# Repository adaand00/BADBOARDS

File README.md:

# BADBOARDS
 Useless keyboards
 
## Current boards

### BB-1 ASCIISTICK
Back to the roots. Gain full control with raw ascii input.

### BB-2 GRIDNAVIGATOR
*Etch-a-sketch* for the 21st century. This keyboard even has additional mouse input.

## Future keyboards

- [ ] One key morse code
- [ ] ascending letters + next
- [ ] Slot machine letters
- [ ] Joystick
- [ ] Frequency control
- [ ] Flute
- [ ] Accelerometer
- [ ] Advanced control panel
- [ ] Shrek

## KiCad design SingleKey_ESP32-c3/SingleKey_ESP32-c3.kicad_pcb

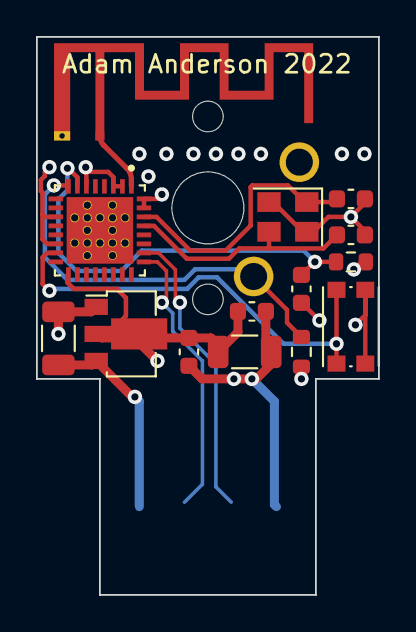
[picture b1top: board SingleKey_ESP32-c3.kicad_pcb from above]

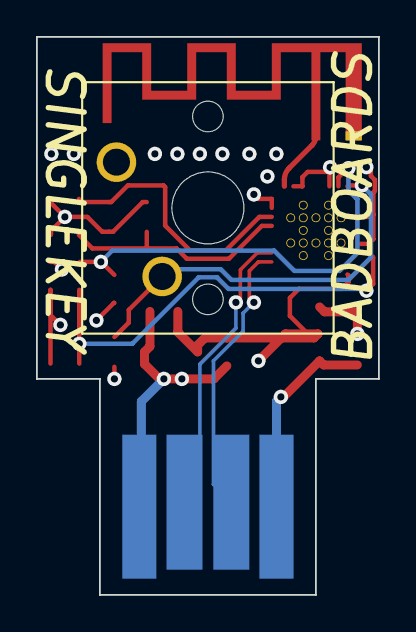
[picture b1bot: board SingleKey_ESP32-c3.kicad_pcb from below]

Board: 4 copper layers, 19.0 x 31.0 mm, 16 parts (2 on the bottom side), 11 nets.

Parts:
AE1: Antenna; Texas_SWRA117D_2.4GHz_Right
C1, C2: 10pF; C_0603_1608Metric
C3, C4: 100n; C_0603_1608Metric
C5: 1uF; C_0603_1608Metric
C7, C8: 10uF; C_1206_3216Metric
J1: USB_A; CONN-USB-A-PCB-TRACES
R1, R2: 1k; R_0603_1608Metric
SW1: SW_Push; SW_Cherry_MX_1.00u_PCB
SW3: SW_Push; SW_Push_1P1T_NO_CK_KMR2
U1: ESP32-C3FH4; QFN50P500X500X90-33N
U2: LM1117-3.3; SOT-89-3
Y1: Crystal_GND24; Oscillator_SMD_Abracon_ASE-4Pin_3.2x2.5mm

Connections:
+3V3: C4.1, C5.1, C8.1, R1.1, R2.1, U1.2 (VDD3P3), U1.3 (VDD3P3), U1.6 (GPIO2), U1.11 (VDD3P3_RTC), U1.14 (GPIO8), U1.17 (VDD3P3_CPU), U1.31 (VDDA), U1.32 (VDDA), U2.2 (VO)
+5V: C7.1, J1.1 (VBUS), U2.3 (VI)
/ANT: AE1.1 (FEED), U1.1 (LNA_IN)
/BTN: R2.2, SW1.2, U1.8 (GPIO3)
/USB_D+: J1.3 (D+), U1.26 (GPIO19)
/USB_D-: J1.2 (D-), U1.25 (GPIO18)
Earth: AE1.2 (PCB_Trace), C1.1, C2.2, C3.2, C4.2, C5.2, C7.2, C8.2, J1.4 (GND), SW1.1, SW3.2, U1.33 (GND), U1.34, U1.35, U1.36, U1.37, U1.38, U1.39, U1.40, U1.41, U1.42, U1.43, U1.44, U1.45, U1.46, U1.47, U1.48, U1.49, U2.1 (GND), Y1.2, Y1.4
unnamed: C1.2, U1.30 (XTAL_P), Y1.1
unnamed: C2.1, U1.29 (XTAL_N), Y1.3
unnamed: C3.1, R1.2, U1.7 (CHIP_EN)
unnamed: SW3.1, U1.15 (GPIO9)

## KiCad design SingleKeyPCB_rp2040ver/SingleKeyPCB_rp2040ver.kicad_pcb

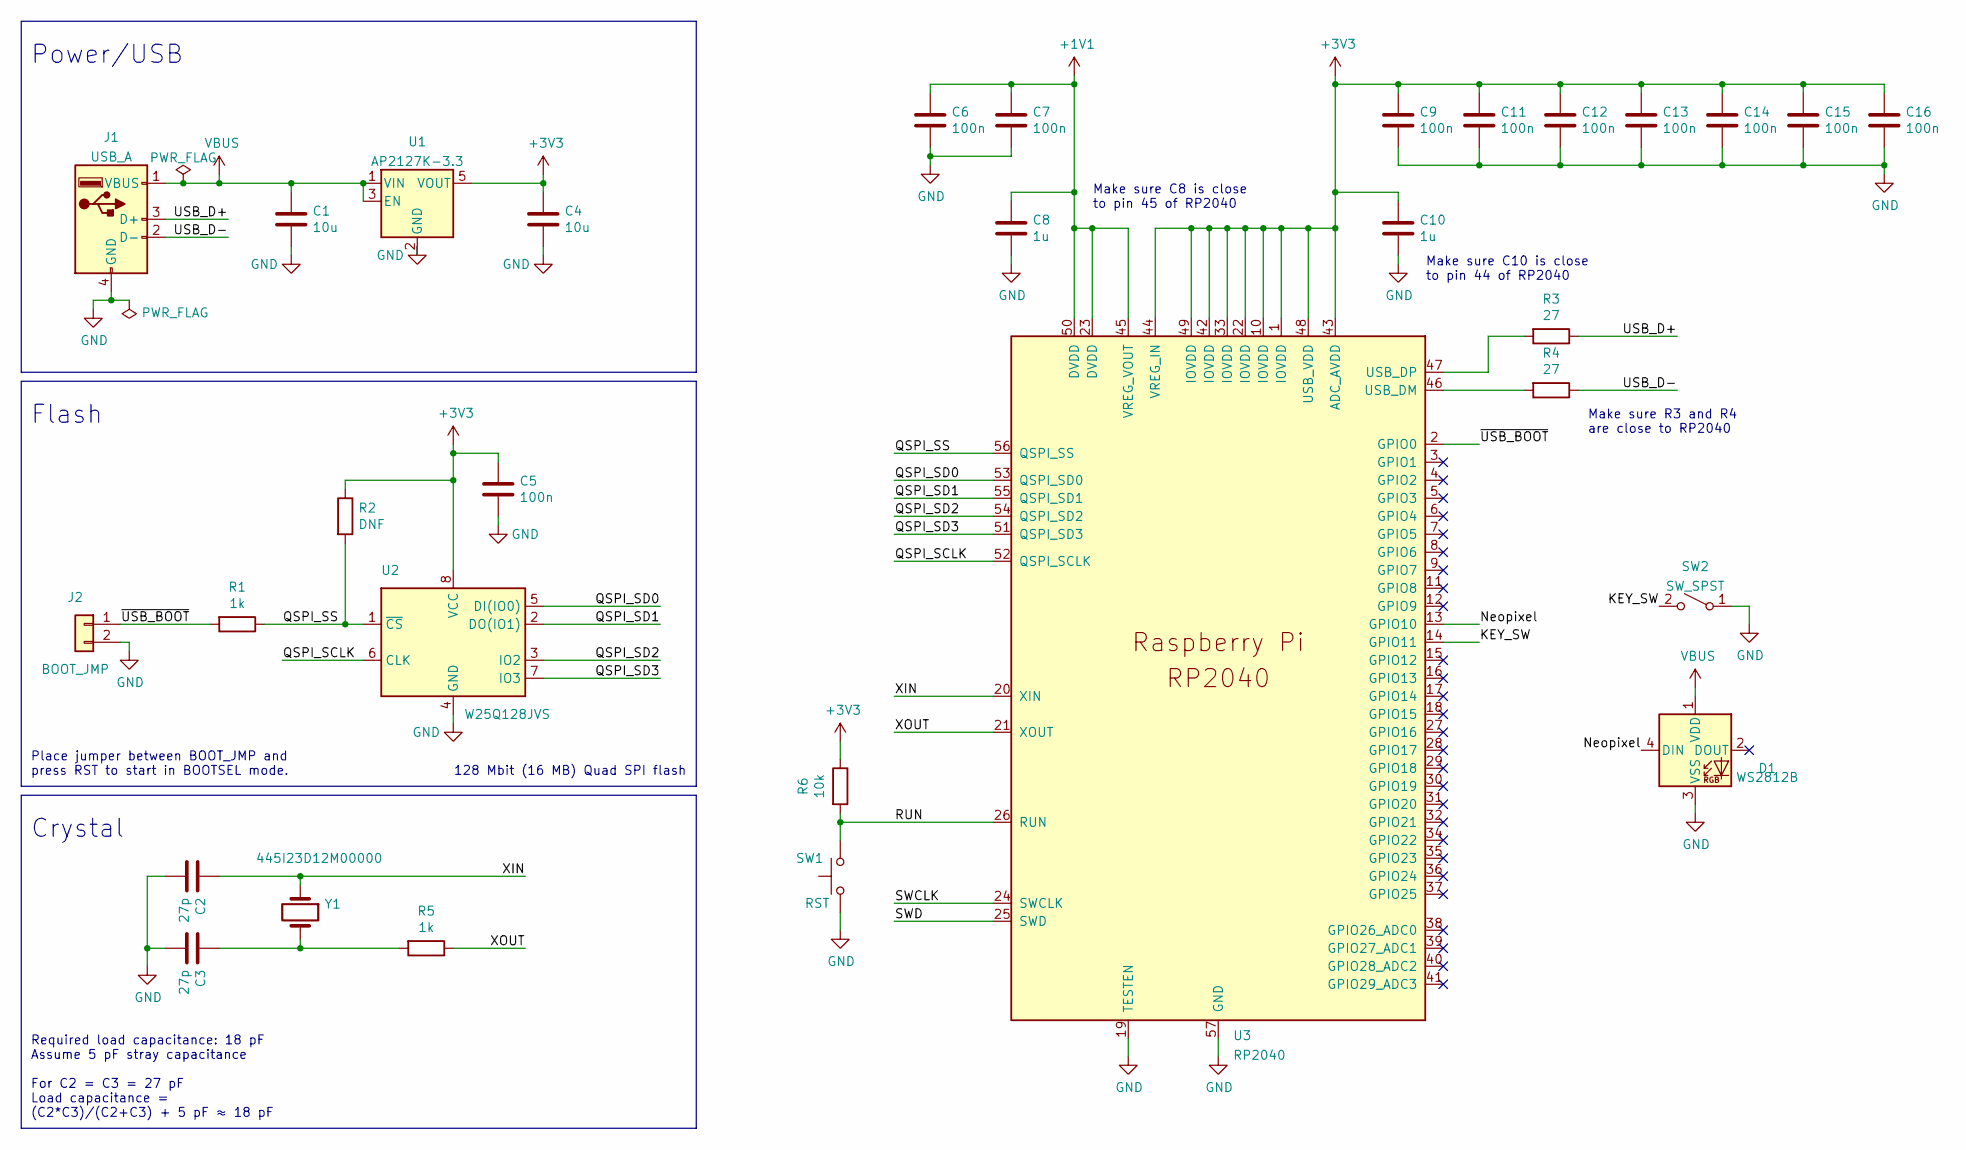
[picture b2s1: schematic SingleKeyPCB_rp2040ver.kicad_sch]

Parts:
C1, C4: 10u; C_0603_1608Metric_Pad1.08x0.95mm_HandSolder
C2, C3: 27p; R_0402_1005Metric_Pad0.72x0.64mm_HandSolder
C5, C6, C7, C9, C11, C12, C13, C14, C15, C16: 100n; R_0402_1005Metric_Pad0.72x0.64mm_HandSolder
C8, C10: 1u; C_0603_1608Metric_Pad1.08x0.95mm_HandSolder
D1: WS2812B; LED_WS2812B_PLCC4_5.0x5.0mm_P3.2mm
J1: USB_A; CONN-USB-A-PCB-TRACES
J2: BOOT_JMP; PinHeader_1x02_P1.27mm_Vertical
R1, R5: 1k; R_0402_1005Metric_Pad0.72x0.64mm_HandSolder
R2: DNF; R_0402_1005Metric_Pad0.72x0.64mm_HandSolder
R3, R4: 27; R_0402_1005Metric_Pad0.72x0.64mm_HandSolder
R6: 10k; R_0402_1005Metric_Pad0.72x0.64mm_HandSolder
SW1: RST; PinHeader_1x02_P1.27mm_Vertical
SW2: SW_SPST; SW_Cherry_MX_1.00u_PCB
U1: AP2127K-3.3; SOT-23-5
U2: W25Q128JVS; WSON-8-1EP_6x5mm_P1.27mm_EP3.4x4.3mm
U3: RP2040; RP2040-QFN-56
Y1: 445I23D12M00000; Crystal_SMD_5032-2Pin_5.0x3.2mm_HandSoldering

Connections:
+1V1: C6.1, C7.1, C8.1, U3.23 (DVDD), U3.45 (VREG_VOUT), U3.50 (DVDD)
+3V3: C4.1, C5.1, C9.1, C10.1, C11.1, C12.1, C13.1, C14.1, C15.1, C16.1, R2.1, R6.1, U1.5 (VOUT), U2.8 (VCC), U3.1 (IOVDD), U3.10 (IOVDD), U3.22 (IOVDD), U3.33 (IOVDD), U3.42 (IOVDD), U3.43 (ADC_AVDD), U3.44 (VREG_IN), U3.48 (USB_VDD), U3.49 (IOVDD)
/KEY_SW: SW2.2 (B), U3.14 (GPIO11)
/Neopixel: D1.4 (DIN), U3.13 (GPIO10)
/QSPI_SCLK: U2.6 (CLK), U3.52 (QSPI_SCLK)
/QSPI_SD0: U2.5 (DI(IO0)), U3.53 (QSPI_SD0)
/QSPI_SD1: U2.2 (DO(IO1)), U3.55 (QSPI_SD1)
/QSPI_SD2: U2.3 (IO2), U3.54 (QSPI_SD2)
/QSPI_SD3: U2.7 (IO3), U3.51 (QSPI_SD3)
/QSPI_SS: R1.1, R2.2, U2.1 (~CS), U3.56 (QSPI_SS)
/RUN: R6.2, SW1.2, U3.26 (RUN)
/SWCLK: U3.24 (SWCLK)
/SWD: U3.25 (SWD)
/USB_D+: J1.3 (D+), R3.1
/USB_D-: J1.2 (D-), R4.1
/XIN: C2.1, U3.20 (XIN), Y1.1
/XOUT: R5.1, U3.21 (XOUT)
/~USB_BOOT: J2.1, R1.2, U3.2 (GPIO0)
GND: C1.2, C2.2, C3.2, C4.2, C5.2, C6.2, C7.2, C8.2, C9.2, C10.2, C11.2, C12.2, C13.2, C14.2, C15.2, C16.2, D1.3 (VSS), J1.4 (GND), J2.2, SW1.1, SW2.1 (A), U1.2 (GND), U2.4 (GND), U2.9, U3.19 (TESTEN), U3.57 (GND)
unnamed: C3.1, R5.2, Y1.2
unnamed: R3.2, U3.47 (USB_DP)
unnamed: R4.2, U3.46 (USB_DM)
VBUS: C1.1, D1.1 (VDD), J1.1 (VBUS), U1.1 (VIN), U1.3 (EN)

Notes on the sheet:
128 Mbit (16 MB) Quad SPI flash
Make sure C10 is close to pin 44 of RP2040
Power/USB
Required load capacitance: 18 pF Assume 5 pF stray capacitance For C2 = C3 = 27 pF Load capacitance = (C2*C3)/(C2+C3) + 5 pF ≈ 18 pF
Crystal
Place jumper between BOOT_JMP and press RST to start in BOOTSEL mode.
Make sure C8 is close to pin 45 of RP2040
Flash
Make sure R3 and R4 are close to RP2040

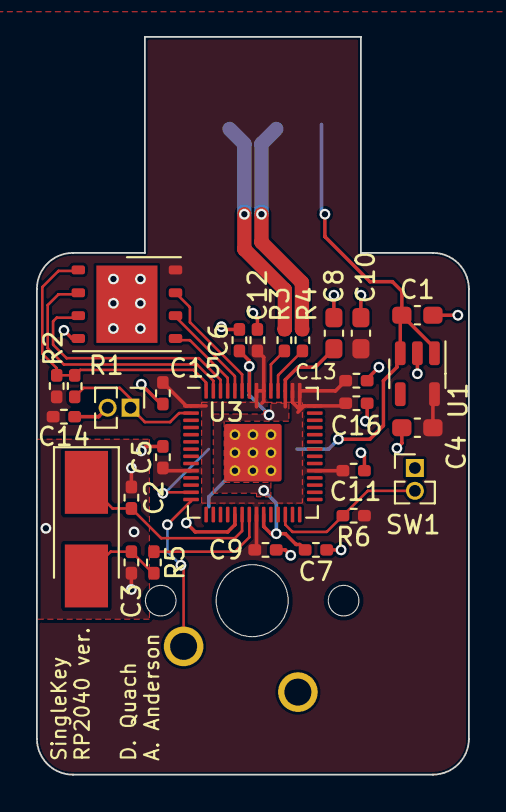
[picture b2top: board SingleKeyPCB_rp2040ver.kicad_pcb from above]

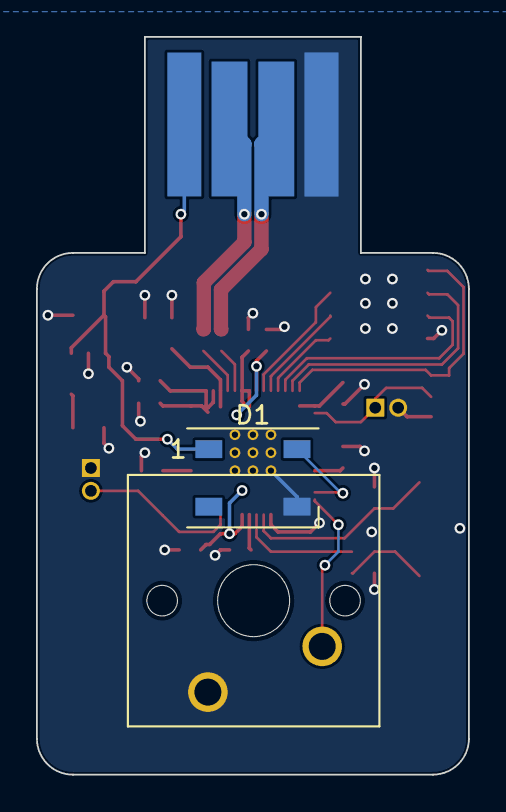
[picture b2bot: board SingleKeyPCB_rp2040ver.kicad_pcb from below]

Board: 2 copper layers, 24.0 x 41.0 mm, 31 parts (3 on the bottom side), 21 nets.

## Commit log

2022-04-08 PCB and code
2022-04-08 Some ideas
2022-04-24 PCB v1
2022-04-24 Add preview when typing
2022-06-09 Start of board 2: GRIDNAVIGATOR
2022-06-17 Mouse code, PCB finished
2022-06-19 add pcb for SingleKey rp2040
2022-06-19 Silkscreen adjustments
2022-09-06 Move enter to other end
2022-10-20 ESP32-c3 Single key
2022-10-23 Add GRBs and iBom
2022-12-01 PCBtweaks
